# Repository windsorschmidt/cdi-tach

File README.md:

# CDI Tachometer

Microcontroller circuit and firmware to read the tachometer signal from a motorcycle CDI module (tested on a 1990 Suzuki DR350S).

The output signal is a ground-referenced pulse of about 40V following each ignition event at a frequency of 1 per two crank revolutions. e.g. a pulse frequency of 60Hz yields 7200RPM.

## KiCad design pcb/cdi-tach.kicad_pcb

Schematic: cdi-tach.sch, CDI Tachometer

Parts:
C1: 100nF; C_0805_HandSoldering; Mouser_PN 77-VJ0805Y104JXXAC
C2, C3: 22uF; C_0805_HandSoldering; Mouser_PN 963-JMK316ABJ226KL-T
C4, C5: 1uF; C_0805_HandSoldering
C6, C10, C12: 100nF; C_0805_HandSoldering
C7: 10uF; C_0805_HandSoldering; Mouser_PN 80-EXV106M025A9BAA
C8, C9: 18pF; C_0805_HandSoldering
C11: 4.7uF; C_0805_HandSoldering
C13: 22nF; C_0805_HandSoldering
D1: SSB44; Diode_SSB44; Mouser_PN 625-SSB44-E3
D4: STATUS_GREEN; LED_0805
F1: 3.7A Polyswitch; Fuse_Resettable; Mouser_PN 652-MF-LSMF185/33X-2
GS1: SPD_PU; GS2
GS2: MODE; GS2
L1: 6.8uH; Inductor_Bourns_SRN6045_6mm; Mouser_PN 652-SRN6045-6R8Y
P1: GND; PINTST
P2: SDA; PINTST
P3: SCL; PINTST
P4: PWR_SPD_TACH; Connector_Micro-Fit-3_SMD_Vertical_6ckt
P7: DEBUG; Pin_Header_Straight_2x03
P8: LCD; Pin_Header_Straight_2x03
R1, R5: 3K; R_0805_HandSoldering
R2: 51.1K; R_0805_HandSoldering
R3: 100K; R_0805_HandSoldering
R4: 14.3K; R_0805_HandSoldering
R6: 100.0K; R_0805_HandSoldering
R7: 12.1K; R_0805_HandSoldering
R8: 39; R_0805_HandSoldering
RP1, RP2, RP3: 4.7K; R_Cat16-4
SW1: A; pushbutton_marquardt_6450
SW2: B; pushbutton_marquardt_6450
SW3: C; pushbutton_marquardt_6450
SW4: D; pushbutton_marquardt_6450
U1: MIC5504-3.3YM5; SOT-23-5
U2: ADP2302ARDZ-5.0; ADP2302_SOIC8; Mouser_PN 584-ADP2302ARDZ5.0R7
U3: STM32F030K6T6; LQFP-32_7x7mm_Pitch0.8mm
Y1: 7A-8.000MAAE-T; crystal_txc_7a_5x3.2mm

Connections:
+3V3: C5.1, C6.2, C10.2, C11.1, C12.1, GS1.2 (G2), GS2.2 (G2), P7.1, P8.1, R8.2, RP1.7 (R2), RP1.8 (R1), RP2.5 (R4), RP2.6 (R3), RP2.7 (R2), RP2.8 (R1), RP3.1, RP3.2, U1.5 (VOUT), U3.1 (VDD), U3.5 (VDDA), U3.17 (VDD); also elsewhere on the board
+5V: C2.1, C3.1, C4.1, L1.2, P4.3, U1.1 (VIN), U1.3 (EN), U2.5 (FB); also elsewhere on the board
+12V: F1.1, P4.4
BTN_A: RP2.2, SW1.1, U3.7 (PA1)
BTN_B: RP2.1, SW2.1, U3.6 (PA0)
BTN_C: RP2.4, SW3.1, U3.20 (PA10)
BTN_D: RP2.3, SW4.1, U3.19 (PA9)
BT_CONN: U3.29 (PB6); also elsewhere on the board
BT_NRST: U3.26 (PB3); also elsewhere on the board
BT_STRM: U3.30 (PB7); also elsewhere on the board
GND: C2.2, C3.2, C4.2, C5.2, C6.1, C7.1, C8.1, C9.1, C10.1, C11.2, C12.2, C13.1, D1.1 (A), P1.1, P4.1, P4.2, P7.2, P8.2, R1.2, R4.2, R7.2, RP3.3, RP3.4, SW1.2, SW2.2, SW3.2, SW4.2, U1.2 (GND), U2.7 (GND), U2.9 (EP), U3.16 (VSS), U3.32 (VSS); also elsewhere on the board
LED_BLANK: U3.14 (PB0); also elsewhere on the board
unnamed: C1.1, D1.2 (K), L1.1, U2.8 (SW)
unnamed: C1.2, U2.1 (BST)
unnamed: C7.2, F1.2, R2.2, R3.2, U2.2 (VIN), U2.3 (EN)
unnamed: C8.2, U3.2 (PF0-OSC_IN), Y1.2
unnamed: C9.2, U3.3 (PF1-OSC_OUT), Y1.1
unnamed: D4.1 (K), U3.25 (PA15)
unnamed: D4.2 (A), R8.1
unnamed: GS1.1 (G1), R5.2
unnamed: GS2.1 (G1), U3.18 (PA8)
unnamed: P2.1, RP1.1, U3.22 (PA12)
unnamed: P3.1, RP1.2, U3.21 (PA11)
unnamed: P4.5, R6.1
unnamed: R1.1, U3.31 (BOOT0)
unnamed: R3.1, U2.4 (PGOOD)
SPEED: P4.6, R5.1, U3.28 (PB5)
SPI_CS: P8.6, RP3.6 (R3), U3.10 (PA4); also elsewhere on the board
SPI_MISO: P8.5, RP3.7 (R2), U3.12 (PA6)
SPI_MOSI: P8.3, RP3.8 (R1), U3.13 (PA7); also elsewhere on the board
SPI_SCK: P8.4, RP3.5 (R4), U3.11 (PA5); also elsewhere on the board
SWCLK: P7.5, U3.24 (PA14)
SWDIO: P7.3, U3.23 (PA13)
TACH: C13.2, R6.2, R7.1, U3.27 (PB4)
USART_RX: P7.4, U3.9 (PA3); also elsewhere on the board
USART_TX: P7.6, U3.8 (PA2); also elsewhere on the board
VBAT: R2.1, R4.1, U3.15 (PB1)

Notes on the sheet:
Exposed pad internally connected to GND pin
This documentation describes Open Hardware and is licensed under the CERN OHL v. 1.2. You may redistribute and modify this documentation under the terms of the CERN OHL v.1.2. (http://ohwr.org/cernohl). This documentation is distributed WITHOUT ANY EXPRESS OR IMPLIED WARRANTY, INCLUDING OF MERCHANT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
For reed-switch type speed sensors, close jumper SPD_PU. Leave open for hall-effect sensors.

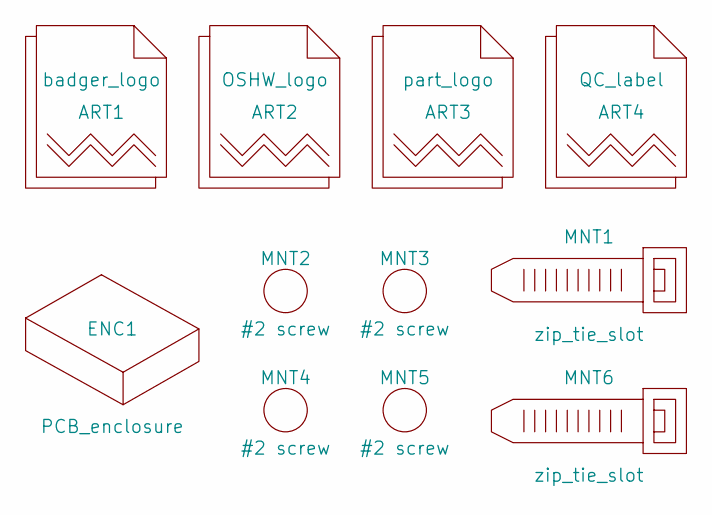
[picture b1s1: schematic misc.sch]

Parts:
ART1: badger_logo; badger_face_logo
ART2: OSHW_logo; Symbol_OSHW-Logo_SilkScreen
ART3: part_logo; tacometer_logo
ART4: QC_label; label_qc
ENC1: PCB_enclosure; pcb_enclosure
MNT1, MNT6: zip_tie_slot; MOUNT_ZIP_TIE
MNT2, MNT3, MNT4, MNT5: #2 screw; Screw_#2

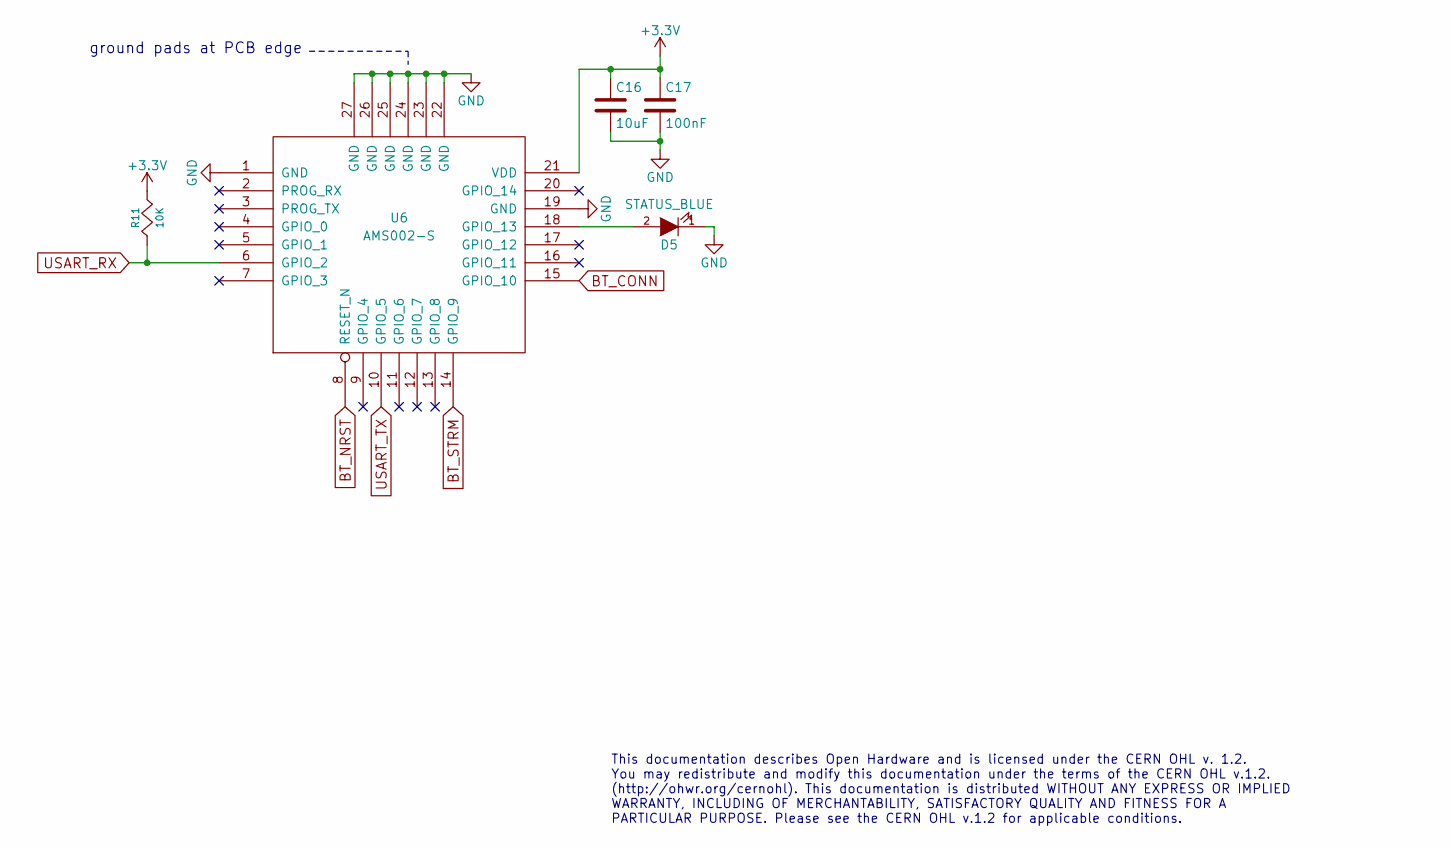
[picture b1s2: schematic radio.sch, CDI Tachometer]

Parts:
C16: 10uF; C_0805_HandSoldering
C17: 100nF; C_0805_HandSoldering
D5: STATUS_BLUE; LED_0805
R11: 10K; R_0805_HandSoldering
U6: AMS002-S

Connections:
+3V3: C16.1, C17.1, R11.1, U6.21 (VDD); also elsewhere on the board
BT_CONN: U6.15 (GPIO_10); also elsewhere on the board
BT_NRST: U6.8 (RESET_N); also elsewhere on the board
BT_STRM: U6.14 (GPIO_9); also elsewhere on the board
GND: C16.2, C17.2, D5.1 (K), U6.1 (GND), U6.19 (GND), U6.22 (GND), U6.23 (GND), U6.24 (GND), U6.25 (GND), U6.26 (GND), U6.27 (GND); also elsewhere on the board
unnamed: D5.2 (A), U6.18 (GPIO_13)
USART_RX: R11.2, U6.6 (GPIO_2); also elsewhere on the board
USART_TX: U6.10 (GPIO_5); also elsewhere on the board

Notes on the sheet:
This documentation describes Open Hardware and is licensed under the CERN OHL v. 1.2. You may redistribute and modify this documentation under the terms of the CERN OHL v.1.2. (http://ohwr.org/cernohl). This documentation is distributed WITHOUT ANY EXPRESS OR IMPLIED WARRANTY, INCLUDING OF MERCHANT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
ground pads at PCB edge

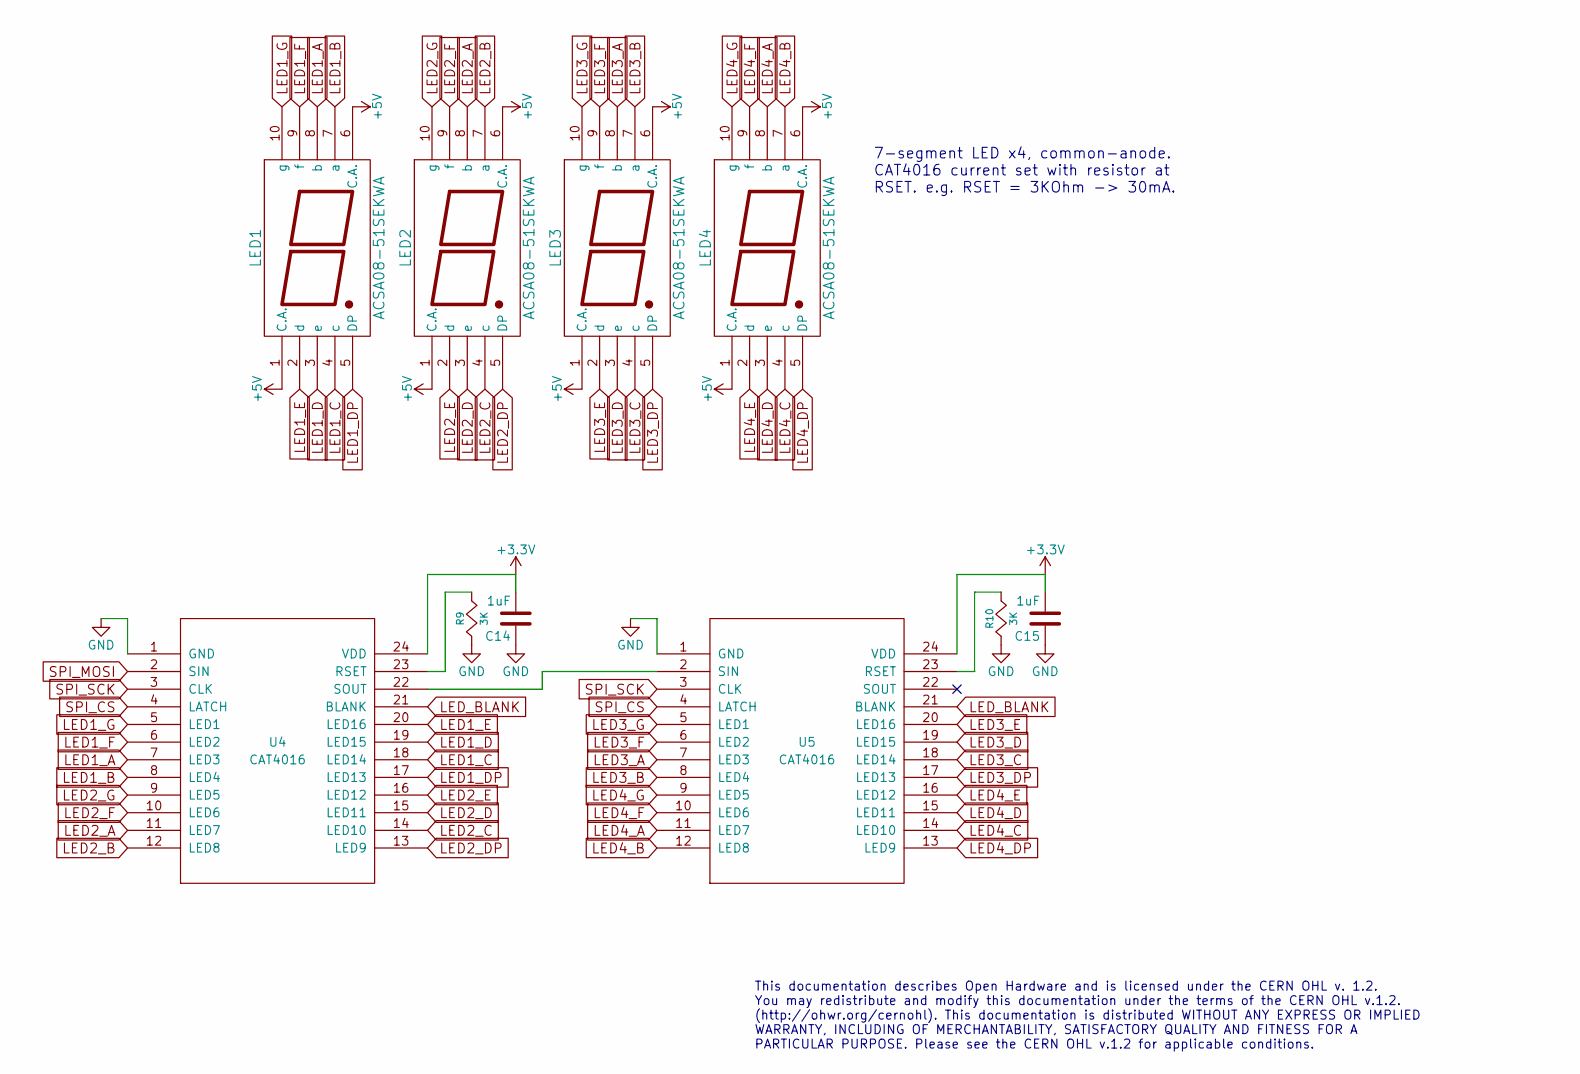
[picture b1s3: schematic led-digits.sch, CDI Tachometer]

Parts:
C14, C15: 1uF; C_0805_HandSoldering
LED1, LED2, LED3, LED4: ACSA08-51SEKWA
R9, R10: 3K; R_0805_HandSoldering
U4, U5: CAT4016; SOIC-24_7.5x15.4mm_Pitch1.27mm

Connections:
+3V3: C14.2, C15.2, U4.24 (VDD), U5.24 (VDD); also elsewhere on the board
+5V: LED1.1 (C.A.), LED1.6 (C.A.), LED2.1 (C.A.), LED2.6 (C.A.), LED3.1 (C.A.), LED3.6 (C.A.), LED4.1 (C.A.), LED4.6 (C.A.); also elsewhere on the board
GND: C14.1, C15.1, R9.2, R10.2, U4.1 (GND), U5.1 (GND); also elsewhere on the board
LED1_A: LED1.8 (b), U4.7 (LED3)
LED1_B: LED1.7 (a), U4.8 (LED4)
LED1_C: LED1.4 (c), U4.18 (LED14)
LED1_D: LED1.3 (e), U4.19 (LED15)
LED1_DP: LED1.5 (DP), U4.17 (LED13)
LED1_E: LED1.2 (d), U4.20 (LED16)
LED1_F: LED1.9 (f), U4.6 (LED2)
LED1_G: LED1.10 (g), U4.5 (LED1)
LED2_A: LED2.8 (b), U4.11 (LED7)
LED2_B: LED2.7 (a), U4.12 (LED8)
LED2_C: LED2.4 (c), U4.14 (LED10)
LED2_D: LED2.3 (e), U4.15 (LED11)
LED2_DP: LED2.5 (DP), U4.13 (LED9)
LED2_E: LED2.2 (d), U4.16 (LED12)
LED2_F: LED2.9 (f), U4.10 (LED6)
LED2_G: LED2.10 (g), U4.9 (LED5)
LED3_A: LED3.8 (b), U5.7 (LED3)
LED3_B: LED3.7 (a), U5.8 (LED4)
LED3_C: LED3.4 (c), U5.18 (LED14)
LED3_D: LED3.3 (e), U5.19 (LED15)
LED3_DP: LED3.5 (DP), U5.17 (LED13)
LED3_E: LED3.2 (d), U5.20 (LED16)
LED3_F: LED3.9 (f), U5.6 (LED2)
LED3_G: LED3.10 (g), U5.5 (LED1)
LED4_A: LED4.8 (b), U5.11 (LED7)
LED4_B: LED4.7 (a), U5.12 (LED8)
LED4_C: LED4.4 (c), U5.14 (LED10)
LED4_D: LED4.3 (e), U5.15 (LED11)
LED4_DP: LED4.5 (DP), U5.13 (LED9)
LED4_E: LED4.2 (d), U5.16 (LED12)
LED4_F: LED4.9 (f), U5.10 (LED6)
LED4_G: LED4.10 (g), U5.9 (LED5)
LED_BLANK: U4.21 (BLANK), U5.21 (BLANK); also elsewhere on the board
unnamed: R9.1, U4.23 (RSET)
unnamed: R10.1, U5.23 (RSET)
unnamed: U4.22 (SOUT), U5.2 (SIN)
SPI_CS: U4.4 (LATCH), U5.4 (LATCH); also elsewhere on the board
SPI_MOSI: U4.2 (SIN); also elsewhere on the board
SPI_SCK: U4.3 (CLK), U5.3 (CLK); also elsewhere on the board

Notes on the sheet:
7-segment LED x4, common-anode. CAT4016 current set with resistor at RSET. e.g. RSET = 3KOhm -> 30mA.
This documentation describes Open Hardware and is licensed under the CERN OHL v. 1.2. You may redistribute and modify this documentation under the terms of the CERN OHL v.1.2. (http://ohwr.org/cernohl). This documentation is distributed WITHOUT ANY EXPRESS OR IMPLIED WARRANTY, INCLUDING OF MERCHANT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

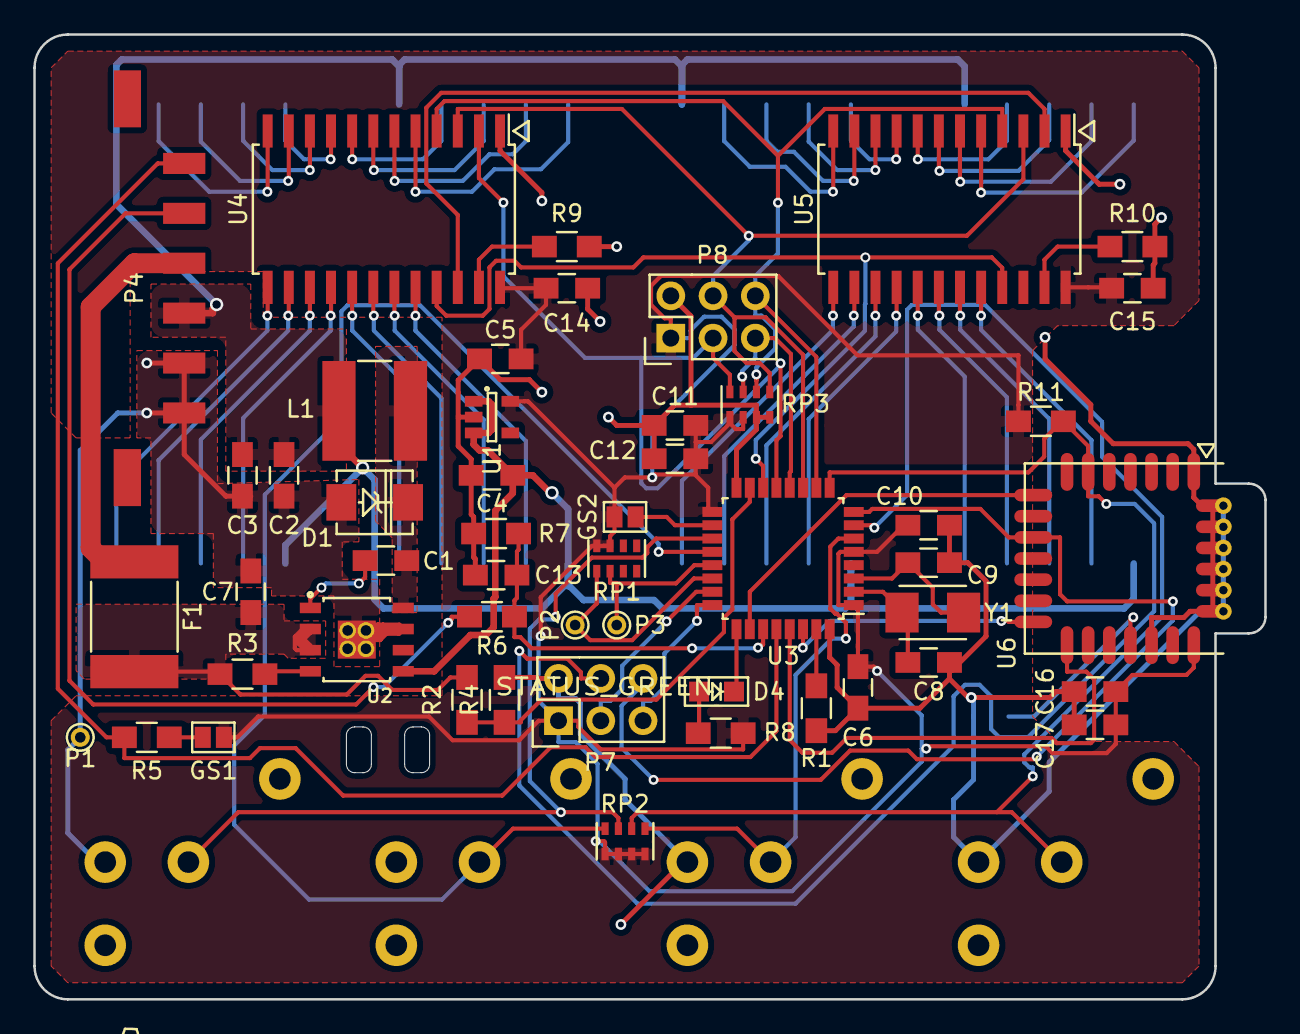
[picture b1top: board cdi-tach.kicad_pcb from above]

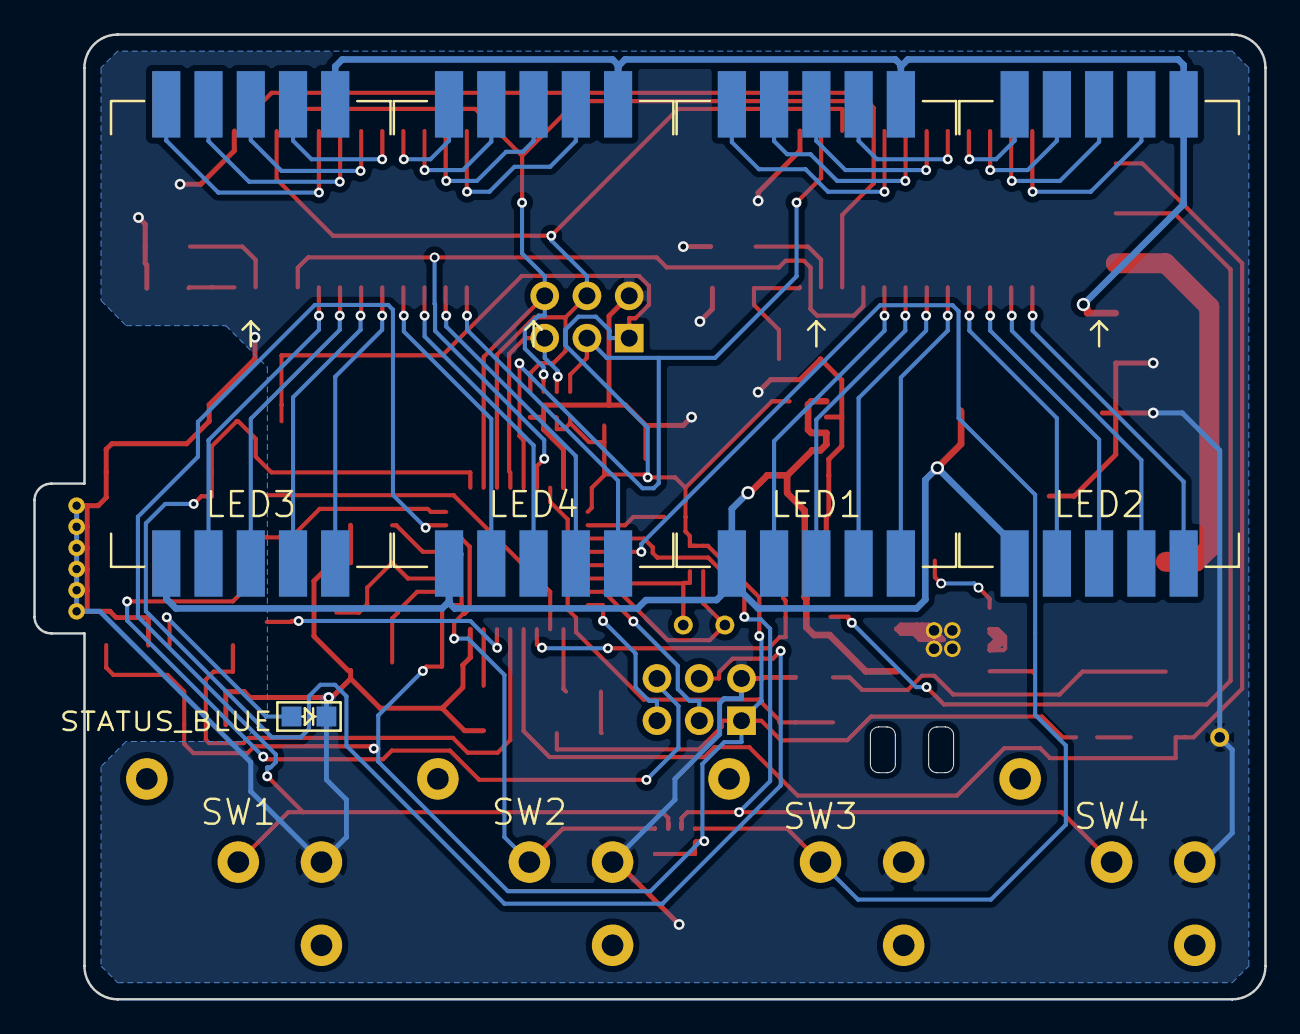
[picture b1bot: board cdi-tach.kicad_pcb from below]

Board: 2 copper layers, 74.0 x 58.0 mm, 65 parts (11 on the bottom side), 73 nets.

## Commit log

2015-07-30 schematic
2015-07-30 didn't need that library hanging around
2015-07-30 readme
2015-07-30 gitignore
2015-07-30 added annotation
2015-08-03 misc edits
2015-08-03 building out schematic
2015-08-03 fix eeschema warning about rescue library
2015-08-10 schematic updates
2015-08-11 adding discrete LEDs
2015-08-12 added input filter schematic for spice simulation
2015-08-12 added datasheets
2015-08-12 updated schematic
2015-08-12 added footprints
2015-08-12 added datasheet for crystal module
2015-08-12 schematic updates. added footprint association. added schematic sheet for PCB artwork and miscellaneous features
2015-08-13 added footprints for artwork
2015-08-13 added netlist
2015-08-13 started pcb layout
2015-08-13 pcb layout
2015-08-15 removed discrete LEDs (probably not enough room). remapped segments to LED drivers for easier routing
2015-08-15 tweaking design rules for autorouter
2015-08-16 added autorouter files
2015-08-16 routing
2015-08-17 added gerber and drill files
2015-08-17 moved fabrication files to subdirectory
2015-08-17 added gerbview project file
2015-08-17 added datasheets for bluetooth module and surface-mound led displays
2015-08-22 hopefully finished trace routing. passes DRC
2015-08-22 adjusted silkscreen references
2015-08-22 removed gerber files; they can be generated from the kicad pcb file whenever
2015-08-22 tweaking vias and silkscreen to avoid overlaps
2015-08-22 tweak colors in gerbv project
2015-08-23 resizing PCB for enclosure
2015-08-30 pcb layout changes to accomodate plastic enclosure
2015-08-31 rewiring some signals LED signals for routing efficiency, and adding voltage divider to measure battery voltage
2015-08-31 added footprint for vertical smd molex micro-fit connector
2015-09-01 added datasheet for molex connector
2015-09-08 preparing to autoroute
